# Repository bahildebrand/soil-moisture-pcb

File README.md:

# soil-moisture-pcb
Capacitive soil moisture sensor routed in KiCad. Uses an Fastnel NRF52840 module, and is powered by a 3.0v coin cell battery.

## PCB Layout

| Front Copper                           | Back Copper |
| ----------------------------------------- | -----
|  |  |

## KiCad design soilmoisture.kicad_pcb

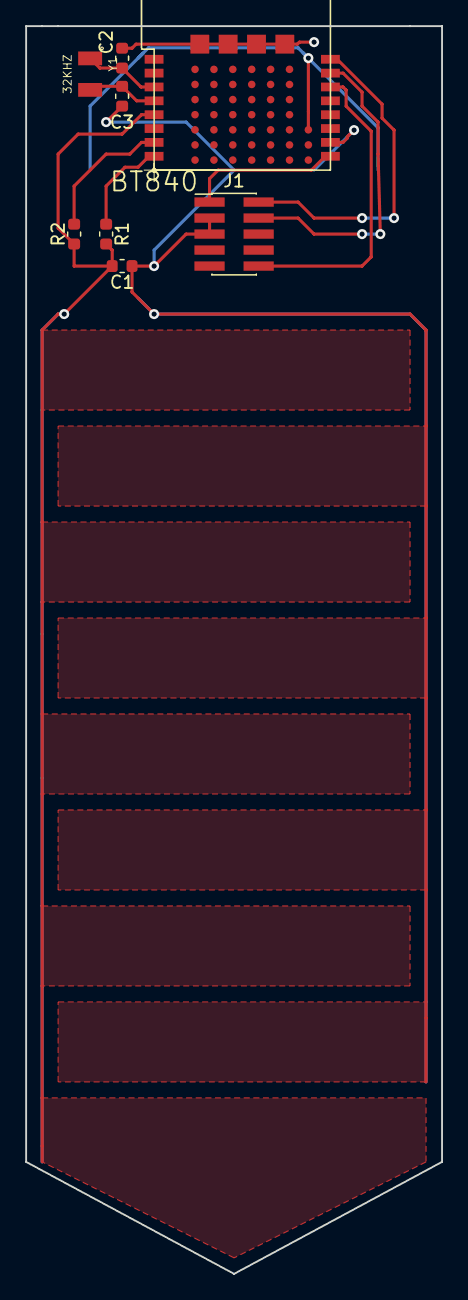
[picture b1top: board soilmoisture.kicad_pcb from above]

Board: 2 copper layers, 33.0 x 99.1 mm, 9 parts (1 on the bottom side), 11 nets.

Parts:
C1: C_Variable; C_0603_1608Metric
C2, C3: 12pF; C_0603_1608Metric
J1: Conn_ARM_JTAG_SWD_10; PinHeader_2x05_P1.27mm_Vertical_SMD
R1: 100k; R_0603_1608Metric
R2: 220; R_0603_1608Metric
U1: BT840; BT840-BT840
U2: BAT-HLD-001
Y1: 32KHZ; XTAL320X150X90

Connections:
+BATT: U1.P$F4, U2.+@1, U2.+@2
/CAP_CHARGE: R1.1, U1.P$7
/CAP_DISCHARGE: R2.2, U1.P$8
/SOIL_READ: C1.1, R1.2, R2.1, U1.P$5
/SWDCLK: J1.4, U1.P$15
/SWDIO: J1.2, U1.P$16
/XL1: C2.1, U1.P$3, Y1.1
/XL2: C3.1, U1.P$4, Y1.2
/nRST: J1.10, U1.P$14
GND: C1.2, C2.2, C3.2, J1.3, J1.5, U1.P$10, U1.P$F0, U1.P$F1, U1.P$F2, U1.P$F3, U2.-
VDD: J1.1, U1.P$9

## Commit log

2018-10-13 Initial schematic/PCB commit
2018-10-13 Add co-planar cap fills
2018-10-13 Add ground plane
2018-10-13 Update README, fixup ground fill
